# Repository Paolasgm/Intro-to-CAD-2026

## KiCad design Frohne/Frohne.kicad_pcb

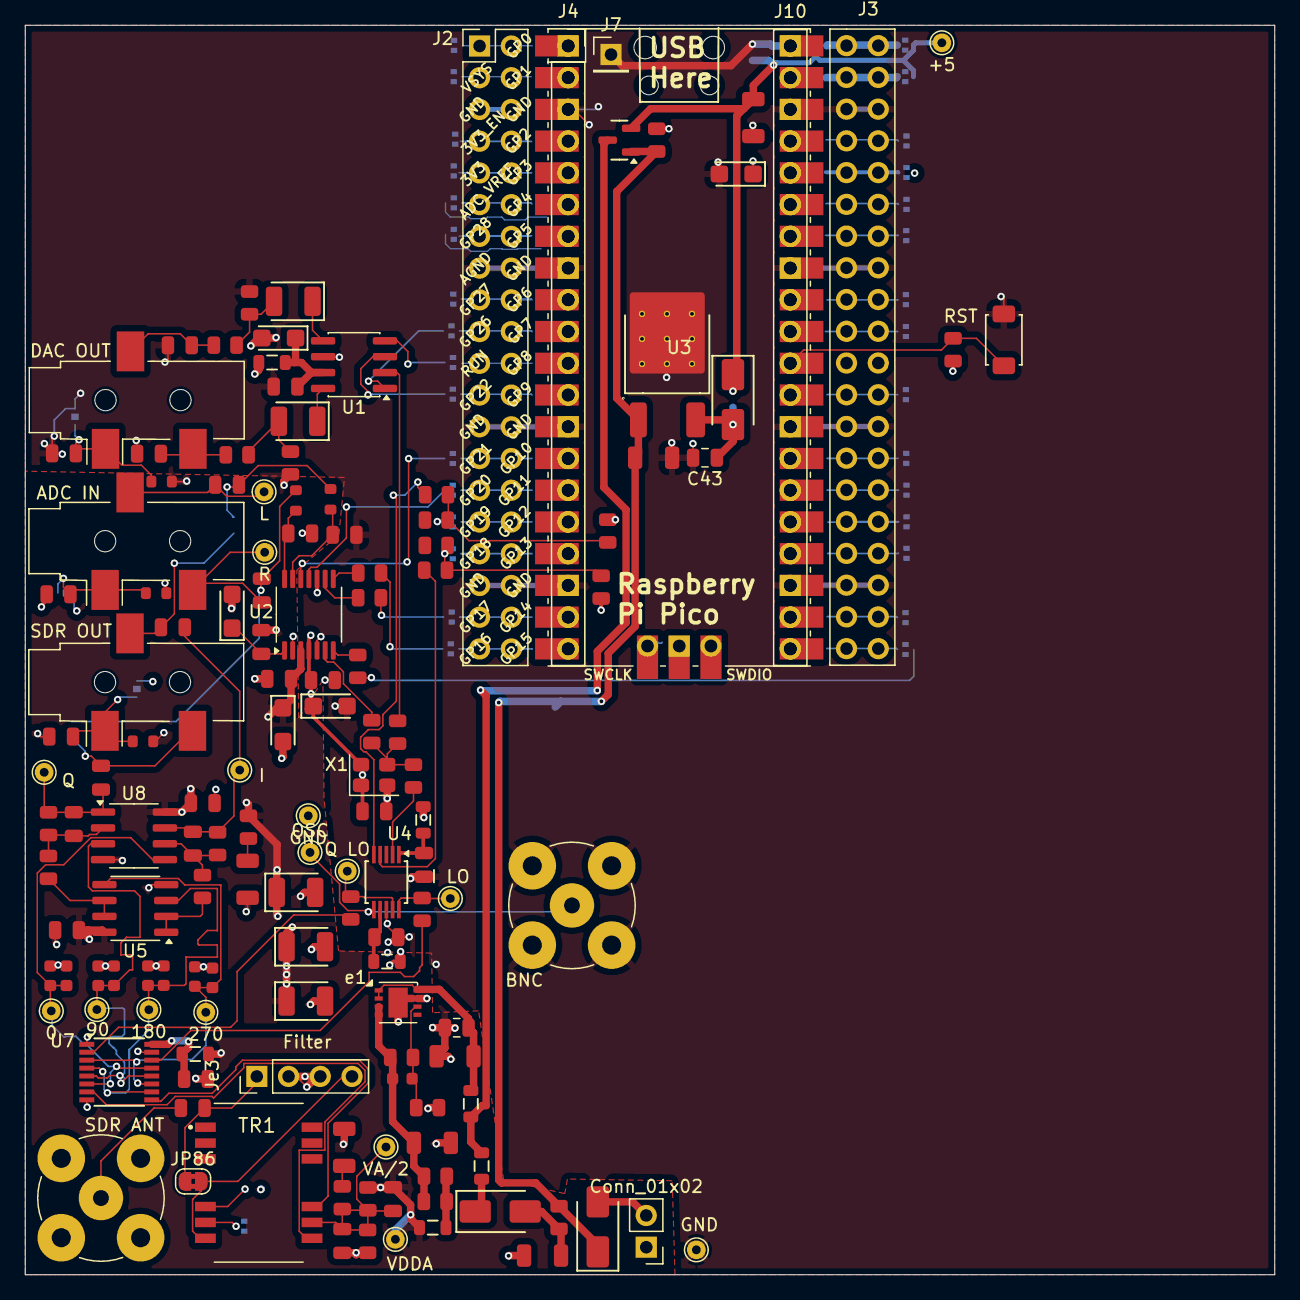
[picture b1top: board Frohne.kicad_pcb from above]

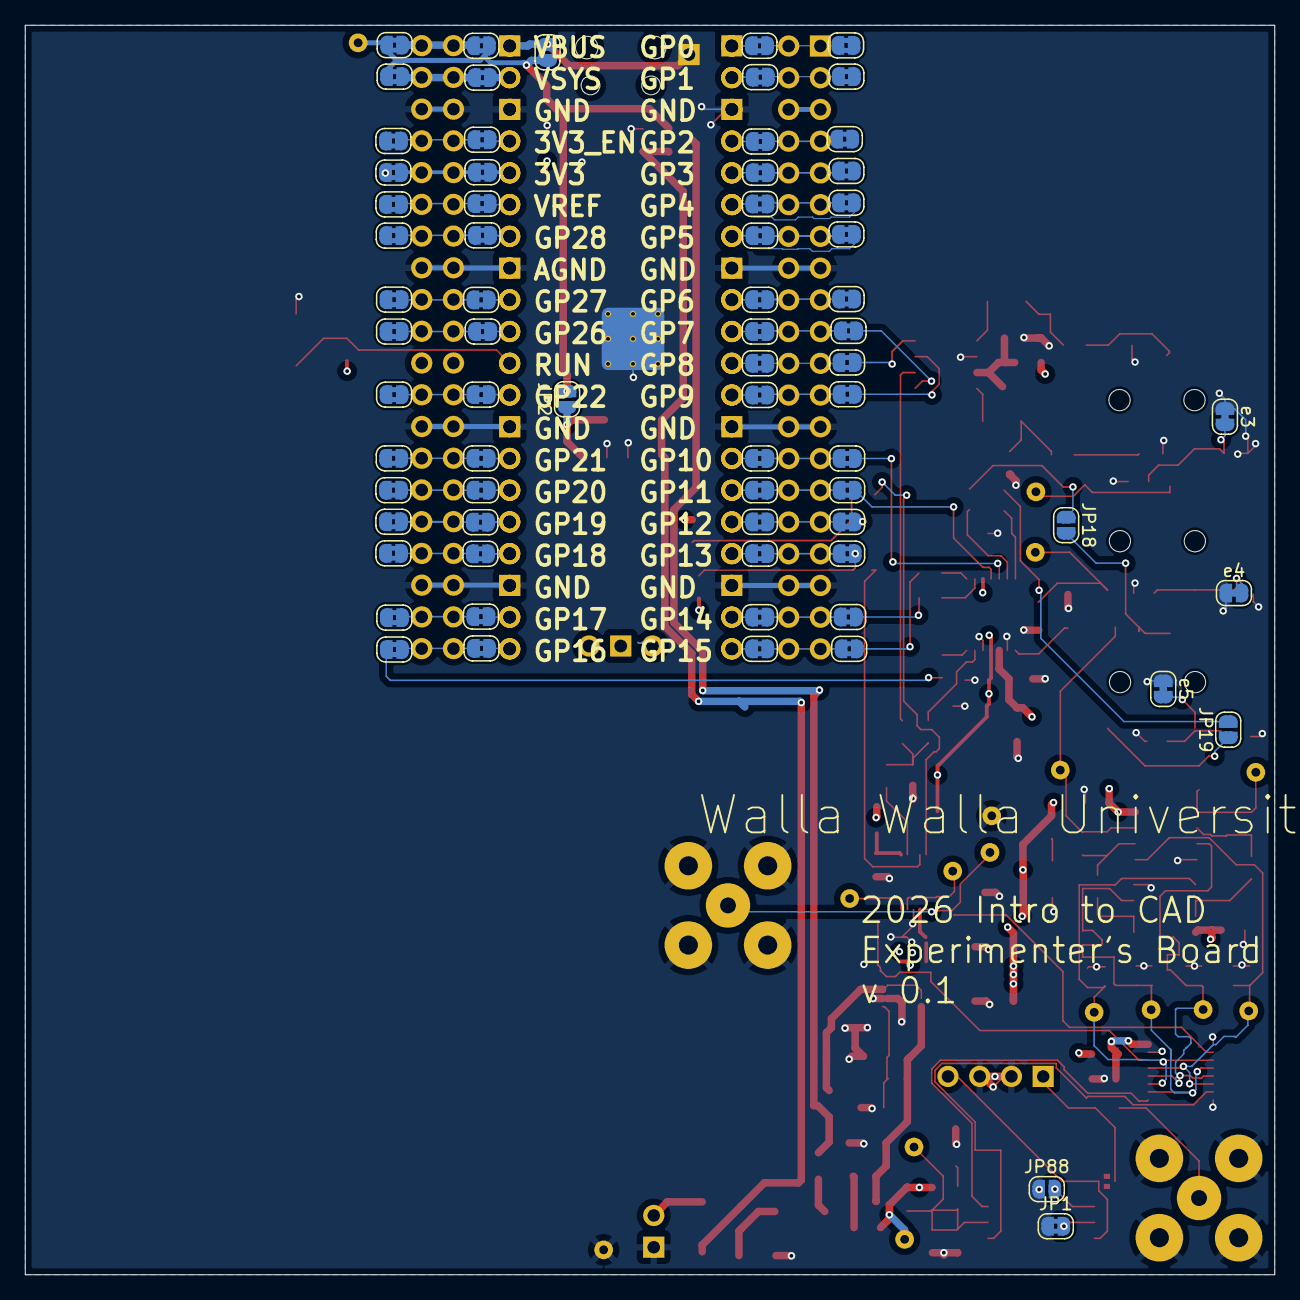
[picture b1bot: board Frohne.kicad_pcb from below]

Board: 4 copper layers, 100.0 x 100.0 mm, 215 parts (71 on the bottom side), 143 nets.

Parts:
C1, C10, C11, C12, C13, C15, C20, C23, C30, C31, C32, C38, C48, C50, C51, C52: 100nF; C_0805
C2, C5, C33, C34, C35, C41, C42: 10uF; C_1206
C3, C4, C21, C29: 1uF; C_0805
C6, C7, C49, C53: 2.2nF; C_0805
C8, C9, C39, C44, C45: 10uF; C_CASE-A-3216-18(mm)
C14, C16, C19, C22, C24, C25, C26, C27: 330pF; C_0603
C17, C36, C37, C46, C47: 100uF; C_CASE-B-3528-21(mm)
C18, C28: 100pF; C_0805
C40: 4.7pF; C_0603
C43, C55: 0.1u; C_0805_2012Metric
D1, D2, D3: SS14; D_SMA
FB1, FB2, FB3, FB4, FB5, FB6, FB7: FB_0805
J1: ADC IN; Jack_3.5mm_CUI_SJ-3523-SMT_Horizontal
J2: Conn_02x20_Counter_Clockwise; PinSocket_2x20_P2.54mm_Vertical_pins1-20
J3: Conn_02x20_Counter_Clockwise; PinSocket_2x20_P2.54mm_Vertical_Counterclockwise_pins21-40
J4: Conn_01x20_Socket; PinSocket_1x20_P2.54mm_Vertical
J5: Conn_01x02; PinHeader_1x02_P2.54mm_Vertical
J7: Conn_01x01_Pin; PinHeader_1x01_P2.54mm_Vertical
J8: BNC; BNC_TEConnectivity_1478204_Vertical
J9: DAC OUT; Jack_3.5mm_CUI_SJ-3523-SMT_Horizontal
J10: Conn_01x20_Socket; PinSocket_1x20_P2.54mm_Vertical-pins21-40
J11: SDR ANT; BNC_TEConnectivity_1478204_Vertical
J12: SDR OUT; Jack_3.5mm_CUI_SJ-3523-SMT_Horizontal
JP1, JP20, JP21, JP22, JP23, JP24, JP25, JP26, JP27, JP28, JP29, JP30, JP31, JP32, JP33, JP34, JP35, JP36, JP37, JP38, JP39, JP40, JP41, JP42, JP43, JP44, JP45, JP46, JP47, JP48, JP49, JP51, JP52, JP53, JP54, JP55, JP56, JP57, JP58, JP59, JP60, JP61, JP62, JP63, JP64, JP65, JP66, JP67, JP68, JP70, JP71, JP72, JP73, JP74, JP75, JP76, JP77, JP78, JP79, JP80, JP81, JP82, JP83, JP86: Jumper_2_Bridged; SolderJumper-2_P1.3mm_Bridged2Bar_RoundedPad1.0x1.5mm
JP2: SolderJumper-2_P1.3mm_Open_RoundedPad1.0x1.5mm
JP18, JP19, JP88: GND_LP_SND; SolderJumper-2_P1.3mm_Open_RoundedPad1.0x1.5mm
JP50: USB Only; SolderJumper-2_P1.3mm_Open_RoundedPad1.0x1.5mm
Je3: Filter; PinHeader_1x04_P2.54mm_Vertical
Q1: AO3401A; Q_SOT-23
R1, R4, R12, R13, R31, R32: 10kΩ; R_0805
R2, R3: 430Ω; R_0603
R5: 33kΩ; R_0805
R6: 12kΩ; R_0805
R7, R10, R11, R20, R21: 1Ω; R_0805
R8, R9: 47Ω; R_0805
R14, R19, R30: 10Ω; R_0603
R15, R23: 4.7kΩ; R_0805
R16, R17, R18, R34, R35, R36, R37, R38: 33Ω; R_0805
R22, R33: 560Ω; R_0805
R24, R25, R26, R27: 100Ω; R_0805
R28: 100kΩ; R_0805
R29: 20kΩ; R_0805
S1: RST; SW_TS-1088-AR02016
TP1: L; TestPoint_THTPad_D1.5mm_Drill0.7mm
TP2: R; TestPoint_THTPad_D1.5mm_Drill0.7mm
TP3: I LO; TestPoint_THTPad_D1.5mm_Drill0.7mm
TP4: Q LO; TestPoint_THTPad_D1.5mm_Drill0.7mm
TP5: OSC; TestPoint_THTPad_D1.5mm_Drill0.7mm
TP6: 180; TestPoint_THTPad_D1.5mm_Drill0.7mm
TP7: 270; TestPoint_THTPad_D1.5mm_Drill0.7mm
TP10, TP12: GND; TestPoint_THTPad_D1.5mm_Drill0.7mm
TP11: VA/2; TestPoint_THTPad_D1.5mm_Drill0.7mm
TP14: 0; TestPoint_THTPad_D1.5mm_Drill0.7mm
TP16: 90; TestPoint_THTPad_D1.5mm_Drill0.7mm
TP17: I; TestPoint_THTPad_D1.5mm_Drill0.7mm
TP18: Q; TestPoint_THTPad_D1.5mm_Drill0.7mm
TP25: +5; TestPoint_THTPad_D1.5mm_Drill0.7mm
TP26: VDDA; TestPoint_THTPad_D1.5mm_Drill0.7mm
TR1: H1102NLT; XFMR_H1102NLT
U1: CJC4334H; SOIC-8_3.9x4.9mm_P1.27mm
U2: PCM1808PWR; TSSOP-14_4.4x5mm_P0.65mm
U3: Pico; RPi_Pico_SMD_TH
U4: MS5351M; MSOP-10_3x3mm_P0.5mm
U5, U8: OPA1612AxD; SOIC-8_3.9x4.9mm_P1.27mm
U6: L78M05ABDT-TR; TO-252-2_L6.5-W6.1-P4.58-LS10.0-TL
U7: SN74CBT3253; SSOP-16_3.9x4.9mm_P0.635mm
X1: YC24.576MUBCE2O; Oscillator_SMD_Abracon_ASE-4Pin_3.2x2.5mm
e1: SGM2205-ADJXTDB8G/TR; DFN-8-1EP_3x3mm_P0.65mm_EP1.55x2.4mm
e3, e4, e5: Groundloop_Insurance; SolderJumper-2_P1.3mm_Bridged_RoundedPad1.0x1.5mm

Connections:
+3.3V: C8.1, C10.2, C39.1, C48.1, FB1.1, FB4.2, FB7.2, J2.3, J3.30 (Pin_11), JP23.1 (A), R15.1, R23.1, R29.1, U2.4 (VDD), U2.10 (MD0), X1.1 (EN), X1.4 (Vdd)
+4.7V: C2.1, D3.1, JP2.2 (B), JP20.1 (A), JP21.1 (A), JP35.2 (B), JP50.2 (B), Q1.2 (S), TP25.1
/BCK: JP83.2 (B), R17.2
/CMOS Oscillator/LO_CLK: R36.1, U4.2 (XA)
/CMOS Oscillator/SCKI: R35.2, U2.6 (SCKI)
/CMOS Oscillator/SCLK: R34.1, U1.2 (SCLK)
/DATA: JP82.2 (B), R18.2
/FMT: JP78.2 (B), U2.12 (FMT)
/I: C29.2, J12.R, JP18.2 (B)
/I_CLK: R37.1, U7.14 (S0)
/LRCK: JP77.2 (B), U1.3 (LRCK)
/MCLK: JP76.2 (B), U1.4 (MCLK)
/MD1: JP79.2 (B), U2.11 (MD1)
/OSC_SCL: R25.1, U4.4 (SCL)
/OSC_SDA: R24.1, U4.5 (SDA)
/Q: C21.1, J12.T, JP19.1 (A)
/Q_CLK: R38.1, U7.2 (S1)
/Raspberry_Pi_Pico/GPIO12: JP80.2 (B), R15.2, R24.2, R27.2
/Raspberry_Pi_Pico/GPIO13: JP81.2 (B), R23.2, R25.2, R26.2
/Raspberry_Pi_Pico/RST: J10.30 (Pin_11), R29.2, S1.1 (A), U3.30 (RUN)
/SDIN: JP75.2 (B), U1.1 (SDIN)
/Si5351a/CLK2: J8.1 (In), TP5.1, U4.6 (CLK2)
/WS: JP34.1 (A), R16.2
GND: C2.2, C5.2, C6.2, C7.2, C8.2, C9.2, C10.1, C11.1, C12.2, C13.1, C14.2, C15.1, C16.2, C17.2, C19.2, C20.1, C22.2, C23.1, C24.2, C25.2, C26.2, C27.2, C30.1, C31.1, C33.2, C34.2, C35.2, C36.2, C37.2, C38.1, C39.2, C41.2, C42.2, C43.2, C44.2, C45.2, C48.2, C49.2, C50.1, C51.1, C52.1, C53.2, C55.2, J2.8 (Pin_33), J2.13, J2.18, J3.23 (Pin_18), J3.28, J3.33 (Pin_8), J3.38 (Pin_3), J4.3, J4.8, J4.13, J4.18, J5.1, J8.2 (Ext), J10.23 (Pin_18), J10.28 (Pin_13), J10.33 (Pin_8), J10.38 (Pin_3), J11.2 (Ext), JP1.1 (A), JP88.1 (A), Je3.2, Je3.3, R4.1, R6.2, R14.2, R19.2, R28.2, R30.2, R31.2, R32.2, S1.2 (B), TP10.1, TP12.1, U1.6 (GND), U2.2 (AGND), U2.5 (DGND), U3.3 (GND), U3.8 (GND), U3.13 (GND), U3.18 (GND), U3.23 (GND), U3.28 (GND), U3.33 (AGND), U3.38 (GND), U4.8 (GND), U5.4 (V-), U6.4 (GND), U7.1 (1~OE), U7.8 (GND), U7.15 (2~OE), U8.4 (V-), X1.2 (GND), e1.7 (GND), e1.9 (PAD), e3.1 (A), e4.1 (A), e5.1 (A)
unnamed: C3.2, J1.R, TP1.1
unnamed: C4.2, J1.T, TP2.1
unnamed: C18.2, C29.1, R12.2, TP17.1, U8.7
unnamed: C21.2, C28.2, R13.2, TP18.1, U8.1
unnamed: C33.1, R11.2
unnamed: C34.1, R10.2
unnamed: C35.1, C40.1, R5.2, R7.1, R20.1, e1.3 (VOUT), e1.4 (VOUT)
unnamed: C42.1, D1.2, R21.1
unnamed: C46.2, R22.1, R32.1
unnamed: C47.2, R31.1, R33.1
unnamed: C49.1, J9.R, R22.2
unnamed: C53.1, J9.T, R33.2
unnamed: D1.1, FB2.2
unnamed: FB5.1, R7.2, R20.2
unnamed: J2.1, JP51.2 (B), JP67.1 (A)
unnamed: J2.2, JP52.2 (B), JP68.1 (A)
unnamed: J2.10, JP58.2 (B), JP75.1 (A)
unnamed: J2.11, JP59.2 (B), JP76.1 (A)
unnamed: J2.12, JP60.2 (B), JP77.1 (A)
unnamed: J2.14, JP61.2 (B), JP78.1 (A)
unnamed: J2.15, JP62.2 (B), JP79.1 (A)
unnamed: J2.16, JP63.2 (B), JP80.1 (A)
unnamed: J2.17, JP64.2 (B), JP81.1 (A)
unnamed: J2.19, JP65.2 (B), JP82.1 (A)
unnamed: J2.20, JP66.2 (B), JP83.1 (A)
unnamed: J2.9, JP57.2 (B), JP74.1 (A)
unnamed: J2.7, JP56.2 (B), JP73.1 (A)
unnamed: J2.6, JP55.2 (B), JP72.1 (A)
unnamed: J2.5, JP54.2 (B), JP71.1 (A)
unnamed: J2.4, JP53.2 (B), JP70.1 (A)
unnamed: J3.40 (Pin_1), JP20.2 (B), JP35.1 (A)
unnamed: J3.39 (Pin_2), JP21.2 (B), JP36.1 (A)
unnamed: J3.31 (Pin_10), JP27.2 (B), JP42.1 (A)
unnamed: J3.29 (Pin_12), JP28.2 (B), JP43.1 (A)
unnamed: J3.27 (Pin_14), JP29.2 (B), JP44.1 (A)
unnamed: J3.26 (Pin_15), JP30.2 (B), JP45.1 (A)
unnamed: J3.25 (Pin_16), JP31.2 (B), JP46.1 (A)
unnamed: J3.24 (Pin_17), JP32.2 (B), JP47.1 (A)
unnamed: J3.22 (Pin_19), JP33.2 (B), JP48.1 (A)
unnamed: J3.21 (Pin_20), JP34.2 (B), JP49.1 (A)
unnamed: J3.32 (Pin_9), JP26.2 (B), JP41.1 (A)
unnamed: J3.34 (Pin_7), JP25.2 (B), JP40.1 (A)
unnamed: J3.35 (Pin_6), JP24.2 (B), JP39.1 (A)
unnamed: J3.36 (Pin_5), JP23.2 (B), JP38.1 (A)
unnamed: J3.37 (Pin_4), JP22.2 (B), JP37.1 (A)
unnamed: J4.1, JP51.1 (A), U3.1 (GPIO0)
unnamed: J4.2, JP52.1 (A), U3.2 (GPIO1)
unnamed: J4.4, JP53.1 (A), U3.4 (GPIO2)
unnamed: J4.5, JP54.1 (A), U3.5 (GPIO3)
unnamed: J4.6, JP55.1 (A), U3.6 (GPIO4)
unnamed: J4.7, JP56.1 (A), U3.7 (GPIO5)
unnamed: J4.9, JP57.1 (A), U3.9 (GPIO6)
unnamed: J4.10, JP58.1 (A), U3.10 (GPIO7)
unnamed: J4.11, JP59.1 (A), U3.11 (GPIO8)
unnamed: J4.12, JP60.1 (A), U3.12 (GPIO9)
unnamed: J4.14, JP61.1 (A), U3.14 (GPIO10)
unnamed: J4.15, JP62.1 (A), U3.15 (GPIO11)
unnamed: J4.16, JP63.1 (A), U3.16 (GPIO12)
unnamed: J4.17, JP64.1 (A), U3.17 (GPIO13)
unnamed: J4.19, JP65.1 (A), U3.19 (GPIO14)
unnamed: J4.20, JP66.1 (A), U3.20 (GPIO15)
unnamed: D2.2, J5.2
unnamed: J7.1, J10.40 (Pin_1), JP50.1 (A), U3.40 (VBUS)
unnamed: J10.39 (Pin_2), JP36.2 (B), U3.39 (VSYS)
unnamed: J10.37 (Pin_4), JP37.2 (B), U3.37 (3V3_EN)
unnamed: J10.36 (Pin_5), JP38.2 (B), U3.36 (3V3)
unnamed: J10.35 (Pin_6), JP39.2 (B), U3.35 (ADC_VREF)
unnamed: J10.34 (Pin_7), JP40.2 (B), U3.34 (GPIO28_ADC2)
unnamed: J10.32 (Pin_9), JP41.2 (B), U3.32 (GPIO27_ADC1)
unnamed: J10.31 (Pin_10), JP42.2 (B), U3.31 (GPIO26_ADC0)
unnamed: J10.29 (Pin_12), JP43.2 (B), U3.29 (GPIO22)
unnamed: J10.27 (Pin_14), JP44.2 (B), U3.27 (GPIO21)
unnamed: J10.26 (Pin_15), JP45.2 (B), U3.26 (GPIO20)
unnamed: J10.25 (Pin_16), JP46.2 (B), U3.25 (GPIO19)
unnamed: J10.24 (Pin_17), JP47.2 (B), U3.24 (GPIO18)
unnamed: J10.22 (Pin_19), JP48.2 (B), U3.22 (GPIO17)
unnamed: J10.21 (Pin_20), JP49.2 (B), U3.21 (GPIO16)
unnamed: C1.1, J11.1 (In)
unnamed: JP1.2 (B), TR1.7 (C_RD)
unnamed: C43.1, D3.2, JP2.1 (A), U6.3 (VOUT)
unnamed: C3.1, JP18.1 (A), R2.1
unnamed: C4.1, JP19.2 (B), R3.1
unnamed: C1.2, JP86.1 (A), Je3.1
unnamed: JP86.2 (B), Je3.4, TR1.8 (RD-)
unnamed: JP88.2 (B), TR1.6 (RD+)
unnamed: FB2.1, FB6.1, Q1.3 (D)
unnamed: C41.1, D2.1, Q1.1 (G), R21.2, R28.1, U6.1 (VIN)
unnamed: C20.2, C32.2, R1.1, R4.2, R10.1, TP11.1, TR1.10 (C_RX)
unnamed: TR1.11 (RX+), U7.9 (2A)
unnamed: TR1.9 (RX-), U7.7 (1A)
unnamed: C47.1, U1.8 (AOUTL)
unnamed: C46.1, U1.5 (AOUTR)
unnamed: C12.1, C45.1, FB7.1, U1.7 (VDD)
unnamed: R17.1, U2.8 (BCK)
unnamed: R18.1, U2.9 (DOUT)
unnamed: R16.1, U2.7 (LRCK)
unnamed: C6.1, R2.2, U2.13 (VINL)
unnamed: C7.1, R3.2, U2.14 (VINR)
unnamed: C11.2, C44.1, U2.1 (VREF)
unnamed: R37.2, TP3.1, U4.10 (CLK0)
unnamed: R38.2, TP4.1, U4.9 (CLK1)
unnamed: C15.2, FB4.1, U4.1 (VDD)
unnamed: C38.2, FB1.2, U4.7 (VDDO)
unnamed: C22.1, C26.1, TP6.1, U5.3 (+), U7.4 (1B3), U7.10 (2B1)
unnamed: R8.1, U5.1, U5.2 (-)
unnamed: C24.1, C27.1, TP7.1, U5.5 (+), U7.3 (1B4), U7.11 (2B2)
unnamed: R9.1, U5.6 (-), U5.7
unnamed: C14.1, C16.1, TP14.1, U7.6 (1B1), U7.13 (2B4), U8.5 (+)
unnamed: C19.1, C25.1, TP16.1, U7.5 (1B2), U7.12 (2B3), U8.3 (+)
unnamed: C23.2, FB3.1, U7.16 (VCC)
unnamed: C28.1, R9.2, R13.1, U8.2 (-)
unnamed: C18.1, R8.2, R12.1, U8.6 (-)
unnamed: R34.2, R35.1, R36.2, X1.3 (OUT)
unnamed: C5.1, C55.1, FB6.2, e1.1 (VIN), e1.2 (VIN), e1.8 (EN)
unnamed: C40.2, R5.1, R6.1, e1.6 (SENSE/ADJ)
unnamed: C50.2, J9.S, R19.1, e3.2 (B)
unnamed: C51.2, J1.S, R14.1, e4.2 (B)
unnamed: C52.2, J12.S, R30.1, e5.2 (B)
VDDA: C9.1, C13.2, C17.1, C30.2, C31.2, C32.1, C36.1, C37.1, FB3.2, FB5.2, R1.2, R11.1, TP26.1, U2.3 (VCC), U5.8 (V+), U8.8 (V+)

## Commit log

2026-01-30 Added a Module Template
2026-01-30 Making module instructions...
2026-01-30 Moved my development to Frohne
2026-01-31 Fixed the rest of the schematic errors
2026-02-01 Fixed a number of things
2026-02-01 More fixes.
2026-02-01 Added DAC
2026-02-02 Tuned length of I and Q.
2026-02-02 Made length of sampling caps the same.
2026-02-03 40 unconnected
2026-02-03 forgot to save
2026-02-04 410 warnings
2026-02-06 Added DAC to readme.
2026-02-10 Removed accidentally added MicroSD-breakout-board/.
2026-02-11 Fixed reference to the pico subsheet
2026-02-11 Fixed reference in root schematic to pico.
2026-02-11 Moved my .kicad_pcb to the main directory.
2026-02-12 Added DAC Amp for Paula and Shaina.
2026-02-12 Some insurance added to the DAC Amp
2026-02-12 Fixed VA/2
2026-02-12 Changes from simulations.
2026-02-12 Forgot the other channel.
2026-02-13 Updated simulations.
